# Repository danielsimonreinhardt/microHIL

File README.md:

# microHIL

A small, self-built hardware-in-the-loop box: switchable relays, digital and
analog I/O, two current-monitored 12 V supply outputs and a CAN interface —
all driven from a PC over a single USB cable.

microHIL is built around an **STM32F446RET** (LQFP64) on a custom PCB. It
enumerates as a USB composite device with **two virtual COM ports**: one
carries a plain ASCII command protocol for the I/O, the other exposes CAN1 as
a standard SLCAN adapter. Both can be used at the same time.

> **Status:** working prototype, in active use on the bench. The firmware,
> the command protocol and the Python host library are stable and verified
> against real hardware; the PCB is at revision v0.1 and has a few documented
> quirks that needed rework (see [`docs/hardware-notes.md`](docs/hardware-notes.md)).
> Project documentation under `docs/` is currently in German.

## Features

| Function | Channels | Notes |
|---|---|---|
| Relays | 4 | dry contacts |
| Digital outputs | 8 | `OUT1-8` |
| Digital inputs | 8 | 12 V level, comparator front end with selectable 5 V/12 V threshold |
| Analog inputs | 4 | calibrated, reported in mV (divider for up to ~13 V) |
| Analog outputs | 2 | DAC + buffer, calibrated, ~0…12.2 V |
| Switchable 12 V outputs | 2 | high-side switch with current sense (mA) and firmware current limiting |
| PWM outputs | 4 | 0…1000 ‰, configurable frequency 1 Hz…20 kHz (`PWMFREQ`, shared by all 4 channels, ceiling scope-verified), shares the output stage with `OUT1-4` (interlocked in firmware) |
| CAN | 1 (+1 reserved) | CAN1 as SLCAN USB adapter; CAN2 reserved for remote control |

Analog channels (`AIN1-4`, `AOUT1-2`, `CURR1-2`) are individually two-point
calibrated against reference instruments, so the protocol speaks physical
units (mV / mA) rather than raw ADC counts — see
[`docs/calibration.md`](docs/calibration.md).

The 12 V outputs are protected in firmware: a per-channel limit (`ILIM`,
default 1200 mA) and a combined 1500 mA budget for the shared polyfuse. A
tripped channel latches off until its request is explicitly withdrawn;
`PWR12FLT?` reports the cause.

## Repository layout

```
firmware/microHIL_fw/   STM32CubeMX + CMake project for the STM32F446RET
host/                   Python client library, test GUI, hardware-free checks
hardware/               KiCad 9 schematic, PCB and Gerbers (rev v0.1)
docs/                   Protocol reference, CAN/SLCAN reference, calibration,
                        hardware notes (German)
```

## USB interfaces

microHIL presents two CDC-ACM functions under the same VID:PID `0483:5740`
(ST's factory VCP IDs — no own USB vendor ID). They are told apart by
interface number, which `host/microhil.py` does automatically:

| Interface | Windows | Linux | Content |
|---|---|---|---|
| 0 | `…&MI_00` | `…-if00` | HIL command protocol — [`docs/protocol.md`](docs/protocol.md) |
| 2 | `…&MI_02` | `…-if02` | CAN1 as SLCAN — [`docs/can-usb.md`](docs/can-usb.md) |

Two ports rather than one multiplexed port, because a COM port can only be
opened once on Windows: this way the test GUI and a CAN tool can run
side by side.

## Command protocol

Line-based ASCII, uppercase, `\n`-terminated requests, `\r\n`-terminated
replies — a plain `readline()` is enough. Values are always integers in
mV/mA.

```
*IDN?                 -> microHIL,fw=0.1.0,SN=2065386A5631
RELAY 1 1             -> OK
IN?                   -> 10110001        (IN1 first)
AIN? 2                -> 3300            (mV, calibrated)
PWR12 1 1             -> OK
CURR? 1               -> 536             (mA)
PWM 1 500             -> OK              (‰ duty cycle)
```

Errors are exactly `ERR ARGS`, `ERR RANGE` or `ERR UNKNOWN`. The full
reference, including the range-checking rules and the board serial number in
`*IDN?`, is in [`docs/protocol.md`](docs/protocol.md).

CAN1 speaks the SLCAN/Lawicel dialect (CAN232-compatible), so it works with
`python-can` (`interface="slcan"`) and, on Linux, as a regular SocketCAN
interface via `slcand`. Two extensions beyond CAN232: `B<bit/s>` for exact
non-standard bitrates and `Y` for a loopback self-test without a bus. See
[`docs/can-usb.md`](docs/can-usb.md).

## Getting started (host)

```bash
pip install -r host/requirements.txt
```

```python
from host.microhil import MicroHIL

with MicroHIL() as hil:          # finds the right COM port by itself
    print(hil.idn())
    hil.set_relay(1, True)
    print(hil.get_ain_mv(2), "mV")
    hil.set_pwr12(1, True)
    print(hil.get_curr_ma(1), "mA")
```

A PySide6 test GUI that exercises every function manually, with a CAN trace
tab, comes with it:

```bash
python host/gui.py
```

Two checks in `host/tests/` run without any hardware attached — they verify
the CAN bit timing against the bxCAN register limits and the SLCAN wire
format in both directions against the real `python-can` driver:

```bash
python host/tests/check_bit_timing.py
python host/tests/check_slcan_wire.py
```

## Building the firmware

Needs the `arm-none-eabi` GCC toolchain, CMake ≥ 3.22 and Ninja. The project
was generated with STM32CubeMX and is set up for the STM32Cube extension for
VS Code, but builds fine from the command line:

```bash
cd firmware/microHIL_fw
cmake --preset Debug
cmake --build --preset Debug
```

Flashing is over SWD with an ST-Link V2, e.g.:

```bash
STM32_Programmer_CLI -c port=SWD -w build/Debug/microHIL_fw.elf -rst
```

With GCC 10.3.1 (the version bundled with STM32CubeIDE 1.10.1, confirmed
working end-to-end 2026-09-09), the linker fails on all three `.ld` files
with `non constant or forward reference address expression for section
.ARM.extab` — the `(READONLY)` section attribute on `.ARM.extab`/`.ARM`/
`.preinit_array`/`.init_array`/`.fini_array` needs GCC 11+ (each occurrence
says so in its own comment). Remove `(READONLY)` from those five section
headers in `STM32F446xx_FLASH.ld` (used by the CMake build) and, for
STM32CubeIDE's own Eclipse build, `STM32F446RETX_FLASH.ld`/`_RAM.ld` too, if
building with GCC 10. A GCC 11+ toolchain doesn't need this.

If you regenerate from `microHIL_fw.ioc`, note that the CAN bit timing is
computed at runtime in `Core/Src/slcan.c` (deliberately not stored in CubeMX)
and that the CDC composite build needs ST's `CompositeBuilder`, which CubeMX
does not emit for the F4 series — it is vendored in
`Middlewares/ST/STM32_USB_Device_Library/Class/CompositeBuilder/`.

## Hardware

- MCU: STM32F446RET, LQFP64, 8 MHz crystal, HSE/PLL clock tree
- Debug: SWD (ST-Link V2)
- CAN1: PB8/PB9, transceiver and 120 Ω termination populated
- CAN2: PB5/PB6, not in service yet (see Roadmap)
- KiCad sources, PCB and Gerbers for rev v0.1 are in [`hardware/`](hardware/)

Board revision v0.1 has known issues that required rework — most notably VBUS
routed straight onto the supply rail, and missing pulldowns on the digital
input comparator stages. All of them are documented, with measurements and
the fixes applied, in [`docs/hardware-notes.md`](docs/hardware-notes.md).
Read that file before building a board from these files.

## Roadmap

- **CAN2 as a remote-control interface.** Drive microHIL from a supervising
  ECU or test bench with the same functions as the USB command protocol.
  Frame layout, addressing and bitrate are still to be defined; the bxCAN
  filter bank split needed for CAN2 to receive at all is already in place
  (`SlaveStartFilterBank = 14` in `Core/Src/can_if.c`).
- **CAN1 against a second real bus node**, plus a scope measurement of the
  actual bit rate.

## License

MIT — see [LICENSE](LICENSE).

Vendored third-party code keeps its own license: the STM32 HAL drivers, CMSIS
and the ST USB device library under `firmware/microHIL_fw/Drivers/` and
`firmware/microHIL_fw/Middlewares/` are © STMicroelectronics / Arm and
licensed under their respective terms (see the `LICENSE.txt` files in those
directories).

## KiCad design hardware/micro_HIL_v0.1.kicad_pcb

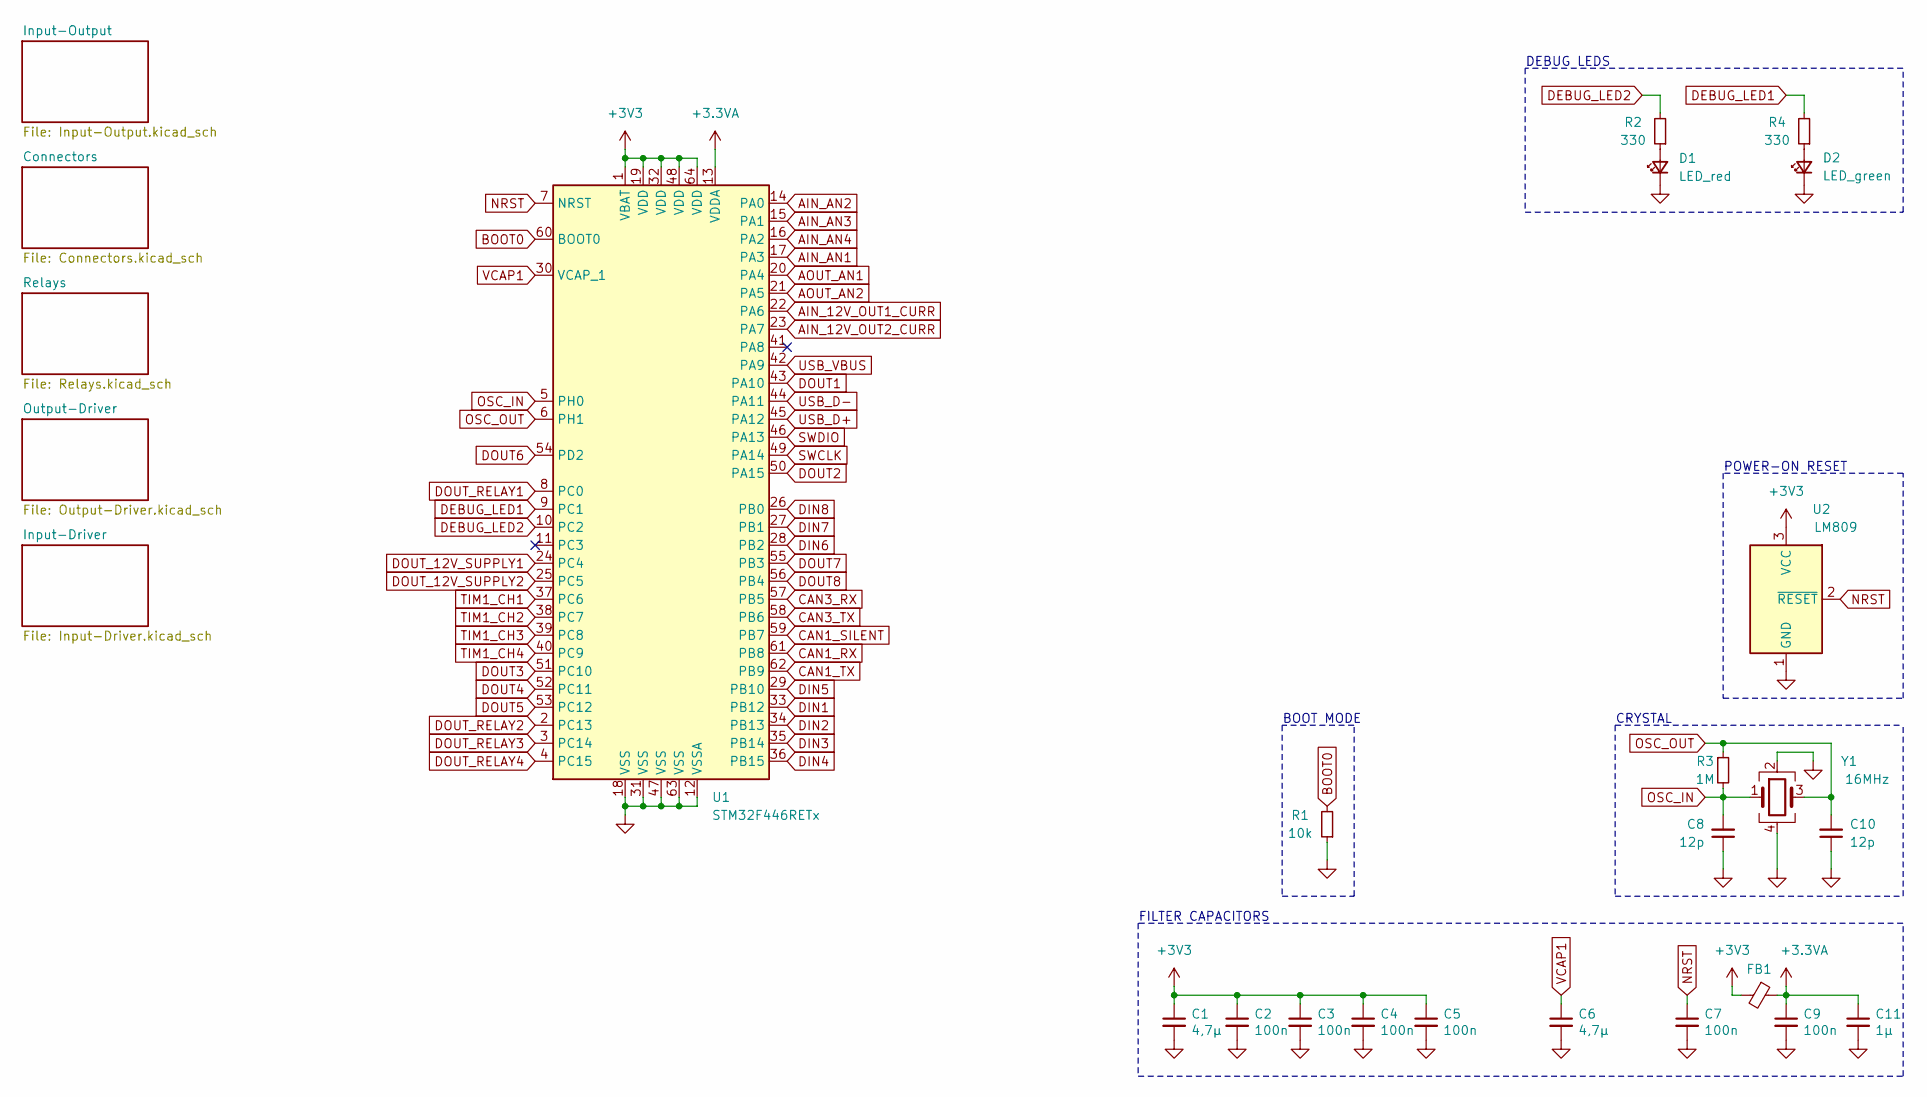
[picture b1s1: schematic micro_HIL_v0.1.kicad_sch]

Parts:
C1, C6: 4,7µ; C_0805_2012Metric
C2, C3, C4, C5, C7, C9: 100n; C_0603_1608Metric
C8, C10: 12p; C_0603_1608Metric
C11: 1µ; C_0603_1608Metric
D1: LED_red; LED_0805_2012Metric
D2: LED_green; LED_0805_2012Metric
FB1: Ferrite_Bead_Small; L_0805_2012Metric
R1: 10k; R_0603_1608Metric
R2, R4: 330; R_0603_1608Metric
R3: 1M; R_0603_1608Metric
U1: STM32F446RETx; LQFP-64_10x10mm_P0.5mm
U2: LM809; SOT-23
Y1: 16MHz; Crystal_SMD_3225-4Pin_3.2x2.5mm

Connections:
+3.3VA: C9.1, C11.1, FB1.1, U1.13 (VDDA)
+3V3: C1.1, C2.1, C3.1, C4.1, C5.1, FB1.2, U1.1 (VBAT), U1.19 (VDD), U1.32 (VDD), U1.48 (VDD), U1.64 (VDD), U2.3 (VCC); also elsewhere on the board
AIN_12V_OUT1_CURR: U1.22 (PA6); also elsewhere on the board
AIN_12V_OUT2_CURR: U1.23 (PA7); also elsewhere on the board
AIN_AN1: U1.17 (PA3); also elsewhere on the board
AIN_AN2: U1.14 (PA0); also elsewhere on the board
AIN_AN3: U1.15 (PA1); also elsewhere on the board
AIN_AN4: U1.16 (PA2); also elsewhere on the board
AOUT_AN1: U1.20 (PA4); also elsewhere on the board
AOUT_AN2: U1.21 (PA5); also elsewhere on the board
BOOT0: R1.2, U1.60 (BOOT0)
CAN1_RX: U1.61 (PB8); also elsewhere on the board
CAN1_SILENT: U1.59 (PB7); also elsewhere on the board
CAN1_TX: U1.62 (PB9); also elsewhere on the board
CAN3_RX: U1.57 (PB5); also elsewhere on the board
CAN3_TX: U1.58 (PB6); also elsewhere on the board
DEBUG_LED1: R4.2, U1.9 (PC1)
DEBUG_LED2: R2.2, U1.10 (PC2)
DIN1: U1.33 (PB12); also elsewhere on the board
DIN2: U1.34 (PB13); also elsewhere on the board
DIN3: U1.35 (PB14); also elsewhere on the board
DIN4: U1.36 (PB15); also elsewhere on the board
DIN5: U1.29 (PB10); also elsewhere on the board
DIN6: U1.28 (PB2); also elsewhere on the board
DIN7: U1.27 (PB1); also elsewhere on the board
DIN8: U1.26 (PB0); also elsewhere on the board
DOUT1: U1.43 (PA10); also elsewhere on the board
DOUT2: U1.50 (PA15); also elsewhere on the board
DOUT3: U1.51 (PC10); also elsewhere on the board
DOUT4: U1.52 (PC11); also elsewhere on the board
DOUT5: U1.53 (PC12); also elsewhere on the board
DOUT6: U1.54 (PD2); also elsewhere on the board
DOUT7: U1.55 (PB3); also elsewhere on the board
DOUT8: U1.56 (PB4); also elsewhere on the board
DOUT_12V_SUPPLY1: U1.24 (PC4); also elsewhere on the board
DOUT_12V_SUPPLY2: U1.25 (PC5); also elsewhere on the board
DOUT_RELAY1: U1.8 (PC0); also elsewhere on the board
DOUT_RELAY2: U1.2 (PC13); also elsewhere on the board
DOUT_RELAY3: U1.3 (PC14); also elsewhere on the board
DOUT_RELAY4: U1.4 (PC15); also elsewhere on the board
GND: C1.2, C2.2, C3.2, C4.2, C5.2, C6.2, C7.2, C8.1, C9.2, C10.1, C11.2, D1.1 (K), D2.1 (K), R1.1, U1.12 (VSSA), U1.18 (VSS), U1.31 (VSS), U1.47 (VSS), U1.63 (VSS), U2.1 (GND), Y1.2, Y1.4; also elsewhere on the board
NRST: C7.1, U1.7 (NRST), U2.2 (~RESET); also elsewhere on the board
unnamed: D1.2 (A), R2.1
unnamed: D2.2 (A), R4.1
OSC_IN: C8.2, R3.2, U1.5 (PH0), Y1.1
OSC_OUT: C10.2, R3.1, U1.6 (PH1), Y1.3
SWCLK: U1.49 (PA14); also elsewhere on the board
SWDIO: U1.46 (PA13); also elsewhere on the board
TIM1_CH1: U1.37 (PC6); also elsewhere on the board
TIM1_CH2: U1.38 (PC7); also elsewhere on the board
TIM1_CH3: U1.39 (PC8); also elsewhere on the board
TIM1_CH4: U1.40 (PC9); also elsewhere on the board
USB_D+: U1.45 (PA12); also elsewhere on the board
USB_D-: U1.44 (PA11); also elsewhere on the board
USB_VBUS: U1.42 (PA9); also elsewhere on the board
VCAP1: C6.1, U1.30 (VCAP_1)

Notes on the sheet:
POWER-ON RESET
BOOT MODE
DEBUG LEDS
FILTER CAPACITORS
CRYSTAL

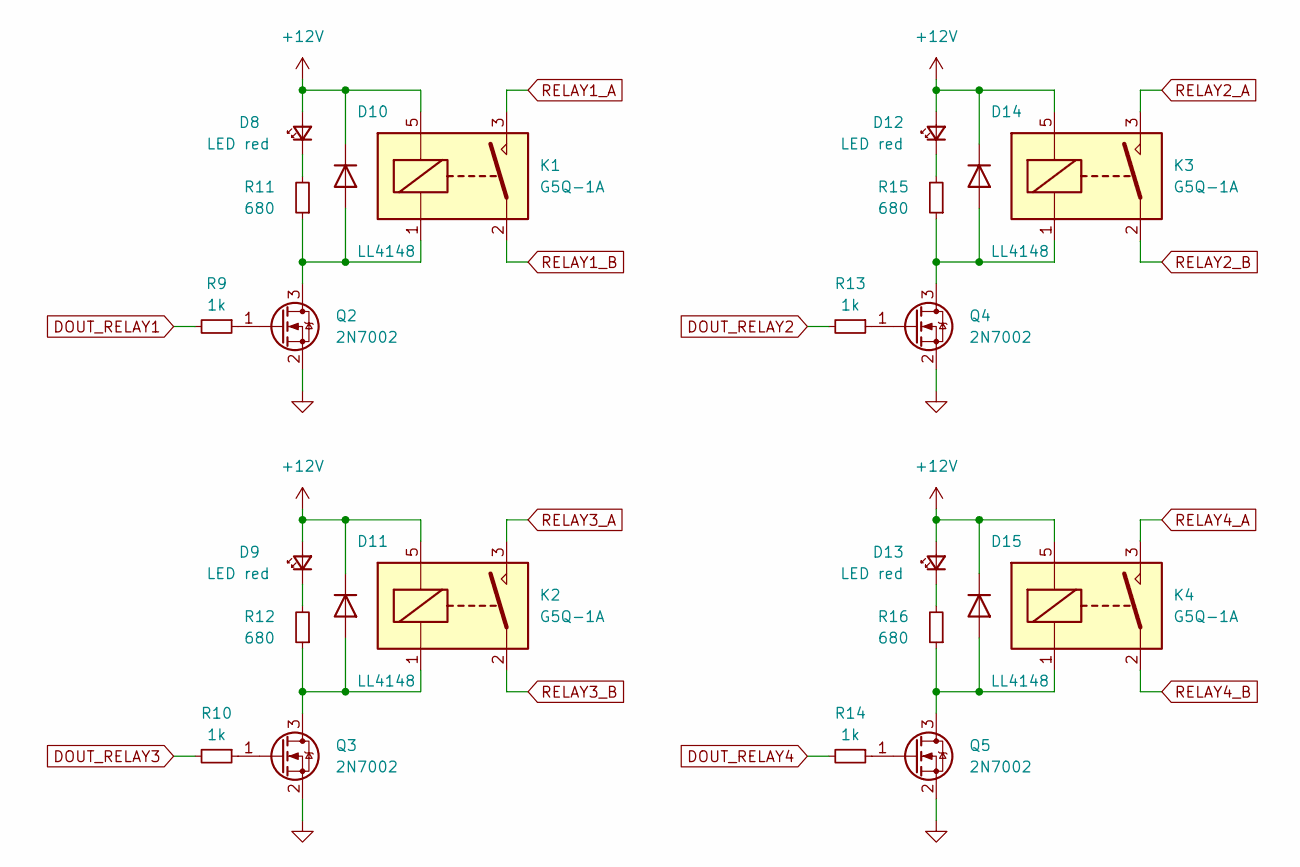
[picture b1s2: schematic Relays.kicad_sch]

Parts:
D8, D9, D12, D13: LED red; LED_D5.0mm
D10, D11, D14, D15: LL4148; D_MiniMELF
K1, K2, K3, K4: G5Q-1A; Relay_SPST_Omron-G5Q-1A
Q2, Q3, Q4, Q5: 2N7002; SOT-23
R9, R10, R13, R14: 1k; R_0603_1608Metric
R11, R12, R15, R16: 680; R_0603_1608Metric

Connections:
+12V: D8.2 (A), D9.2 (A), D10.1 (K), D11.1 (K), D12.2 (A), D13.2 (A), D14.1 (K), D15.1 (K), K1.5, K2.5, K3.5, K4.5; also elsewhere on the board
DOUT_RELAY1: R9.2; also elsewhere on the board
DOUT_RELAY2: R13.2; also elsewhere on the board
DOUT_RELAY3: R10.2; also elsewhere on the board
DOUT_RELAY4: R14.2; also elsewhere on the board
GND: Q2.2 (S), Q3.2 (S), Q4.2 (S), Q5.2 (S); also elsewhere on the board
unnamed: D8.1 (K), R11.2
unnamed: D9.1 (K), R12.2
unnamed: D10.2 (A), K1.1, Q2.3 (D), R11.1
unnamed: D11.2 (A), K2.1, Q3.3 (D), R12.1
unnamed: D12.1 (K), R15.2
unnamed: D13.1 (K), R16.2
unnamed: D14.2 (A), K3.1, Q4.3 (D), R15.1
unnamed: D15.2 (A), K4.1, Q5.3 (D), R16.1
unnamed: Q2.1 (G), R9.1
unnamed: Q3.1 (G), R10.1
unnamed: Q4.1 (G), R13.1
unnamed: Q5.1 (G), R14.1
RELAY1_A: K1.3; also elsewhere on the board
RELAY1_B: K1.2; also elsewhere on the board
RELAY2_A: K3.3; also elsewhere on the board
RELAY2_B: K3.2; also elsewhere on the board
RELAY3_A: K2.3; also elsewhere on the board
RELAY3_B: K2.2; also elsewhere on the board
RELAY4_A: K4.3; also elsewhere on the board
RELAY4_B: K4.2; also elsewhere on the board

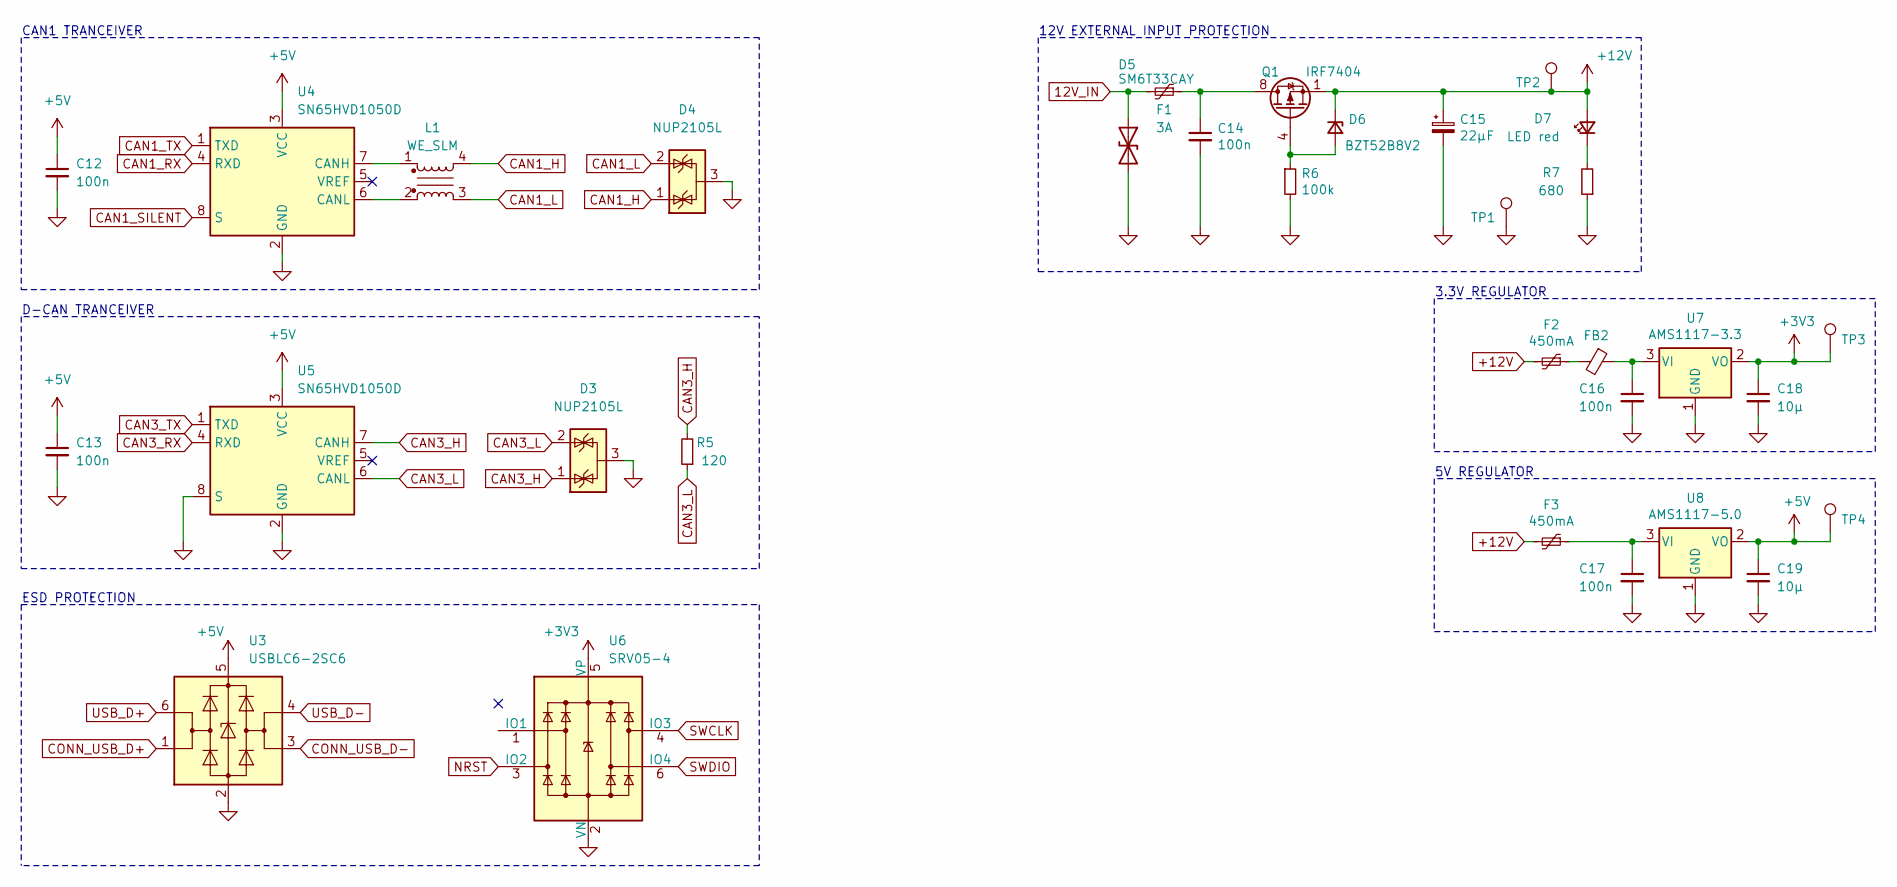
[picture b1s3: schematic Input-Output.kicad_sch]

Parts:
C12, C13, C14, C16, C17: 100n; C_0603_1608Metric
C15: 22µF; CP_Elec_6.3x5.9
C18, C19: 10µ; C_0805_2012Metric
D3, D4: NUP2105L; SOT-23
D5: SM6T33CAY; D_SMB_Handsoldering
D6: BZT52B8V2; D_SOD-123
D7: LED red; LED_D5.0mm
F1: 3A; Fuse_1812_4532Metric
F2, F3: 450mA; Fuse_1210_3225Metric
FB2: Ferrite_Bead_Small; L_0805_2012Metric
L1: WE_SLM; L_CommonMode_Wuerth_WE-SLM
Q1: IRF7404; SOIC-8_3.9x4.9mm_P1.27mm
R5: 120; R_0603_1608Metric
R6: 100k; R_0603_1608Metric
R7: 680; R_0603_1608Metric
TP1: TestPoint; Pin_D1.1mm_L8.5mm_W2.5mm_FlatFork
TP2, TP3, TP4: TestPoint; TestPoint_Pad_D1.0mm
U3: USBLC6-2SC6; SOT-23-6
U4, U5: SN65HVD1050D; SOIC-8_3.9x4.9mm_P1.27mm
U6: SRV05-4; SOT-23-6
U7: AMS1117-3.3; SOT-223-3_TabPin2
U8: AMS1117-5.0; SOT-223-3_TabPin2

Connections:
12V_IN: D5.1 (A1), F1.2; also elsewhere on the board
+3V3: C18.1, TP3.1, U6.5 (VP), U7.2 (VO); also elsewhere on the board
+5V: C12.1, C13.1, C19.1, TP4.1, U3.5 (VBUS), U4.3 (VCC), U5.3 (VCC), U8.2 (VO); also elsewhere on the board
+12V: C15.1, D6.1 (K), D7.2 (A), F2.2, F3.2, Q1.1 (S), Q1.2 (S), Q1.3 (S), TP2.1; also elsewhere on the board
CAN1_H: D4.1 (K), L1.4; also elsewhere on the board
CAN1_L: D4.2 (K), L1.3; also elsewhere on the board
CAN1_RX: U4.4 (RXD); also elsewhere on the board
CAN1_SILENT: U4.8 (S); also elsewhere on the board
CAN1_TX: U4.1 (TXD); also elsewhere on the board
CAN3_H: D3.1 (K), R5.2, U5.7 (CANH); also elsewhere on the board
CAN3_L: D3.2 (K), R5.1, U5.6 (CANL); also elsewhere on the board
CAN3_RX: U5.4 (RXD); also elsewhere on the board
CAN3_TX: U5.1 (TXD); also elsewhere on the board
CONN_USB_D+: U3.1 (I/O1); also elsewhere on the board
CONN_USB_D-: U3.3 (I/O2); also elsewhere on the board
GND: C12.2, C13.2, C14.2, C15.2, C16.2, C17.2, C18.2, C19.2, D3.3 (A), D4.3 (A), D5.2 (A2), R6.2, R7.1, TP1.1, U3.2 (GND), U4.2 (GND), U5.2 (GND), U5.8 (S), U6.2 (VN), U7.1 (GND), U8.1 (GND); also elsewhere on the board
NRST: U6.3 (IO2); also elsewhere on the board
unnamed: C14.1, F1.1, Q1.5 (D), Q1.6 (D), Q1.7 (D), Q1.8 (D)
unnamed: C16.1, FB2.1, U7.3 (VI)
unnamed: C17.1, F3.1, U8.3 (VI)
unnamed: D6.2 (A), Q1.4 (G), R6.1
unnamed: D7.1 (K), R7.2
unnamed: F2.1, FB2.2
unnamed: L1.1, U4.7 (CANH)
unnamed: L1.2, U4.6 (CANL)
SWCLK: U6.4 (IO3); also elsewhere on the board
SWDIO: U6.6 (IO4); also elsewhere on the board
USB_D+: U3.6 (I/O1); also elsewhere on the board
USB_D-: U3.4 (I/O2); also elsewhere on the board

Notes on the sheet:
12V EXTERNAL INPUT PROTECTION
5V REGULATOR
3.3V REGULATOR
D-CAN TRANCEIVER
CAN1 TRANCEIVER
ESD PROTECTION

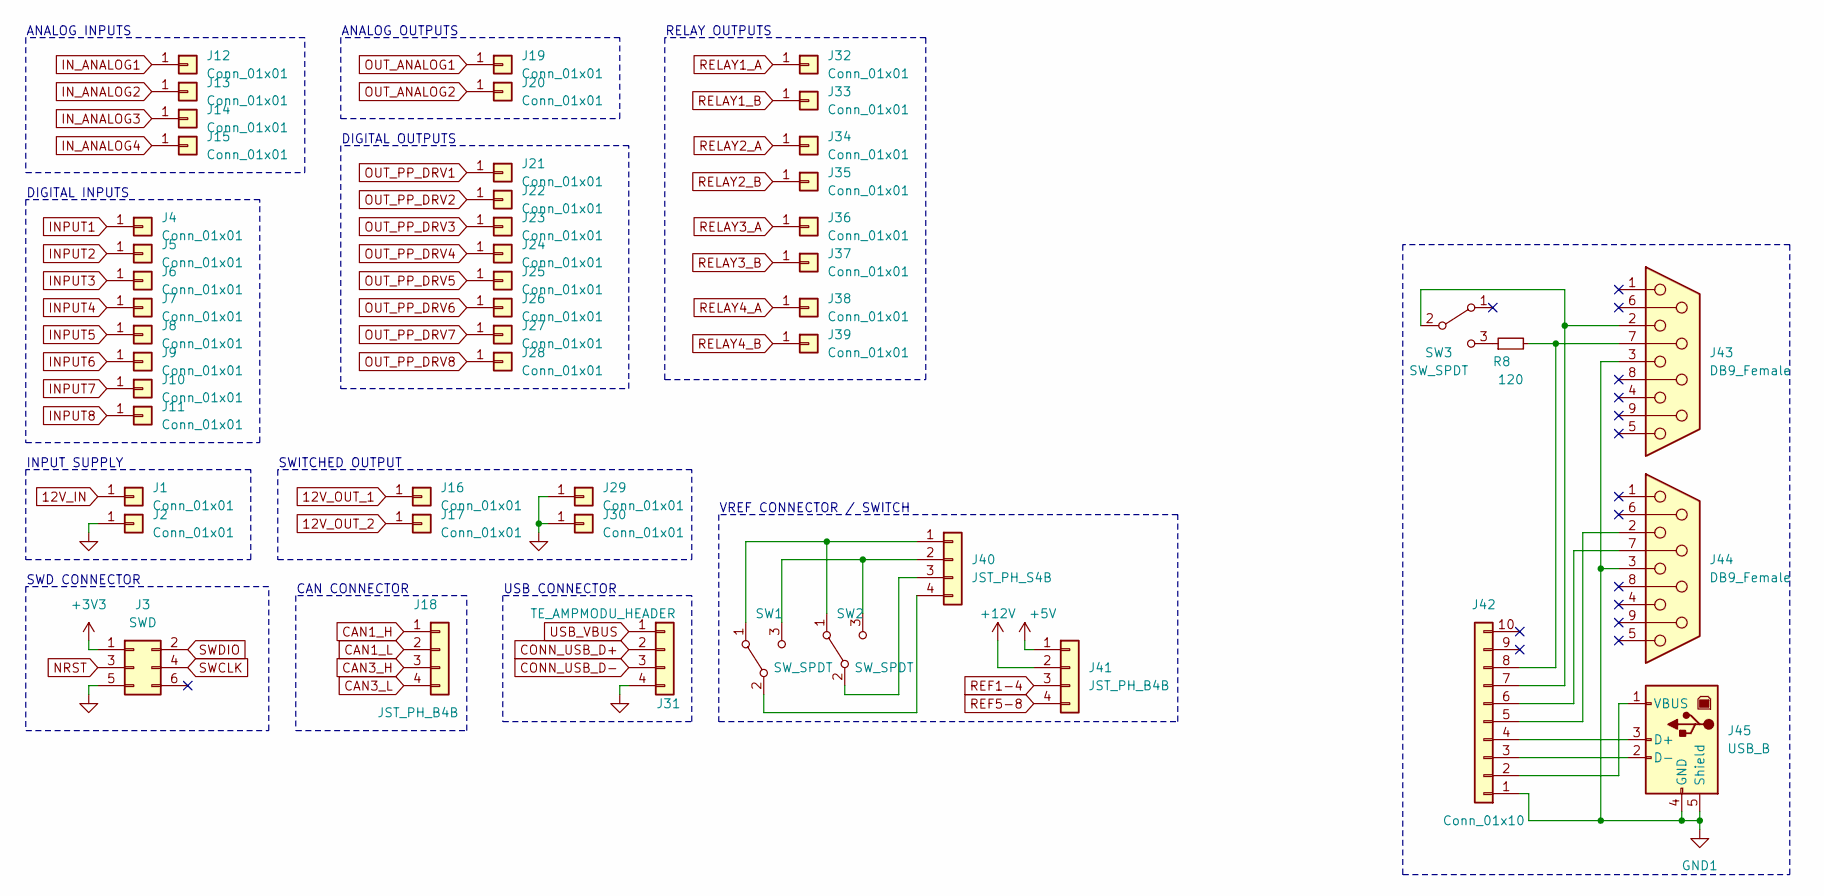
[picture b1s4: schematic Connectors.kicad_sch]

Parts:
J1, J2, J4, J5, J6, J7, J8, J9, J10, J11, J12, J13, J14, J15, J16, J17, J19, J20, J21, J22, J23, J24, J25, J26, J27, J28, J29, J30, J32, J33, J34, J35, J36, J37, J38, J39: Conn_01x01; Hirschmann_SEP_2630_S1,9
J3: SWD; IDC-Header_2x03_P2.54mm_Vertical
J18, J41: JST_PH_B4B; JST_PH_B4B-PH-K_1x04_P2.00mm_Vertical
J31: TE_AMPMODU_HEADER; PinHeader_1x04_P2.54mm_Vertical
J40: JST_PH_S4B; JST_PH_S4B-PH-K_1x04_P2.00mm_Horizontal
J42: Conn_01x10; TE_3-1445056-0
J43, J44: DB9_Female; DSUB-9_Female_Vertical_P2.77x2.84mm_MountingHoles
J45: USB_B; USB_B_TE_5787834_Vertical
R8: 120; R_0603_1608Metric
SW1, SW2, SW3: SW_SPDT; TerminalBlock_bornier-3_P5.08mm

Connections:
12V_IN: J1.1; also elsewhere on the board
12V_OUT_1: J16.1; also elsewhere on the board
12V_OUT_2: J17.1; also elsewhere on the board
+3V3: J3.1; also elsewhere on the board
+5V: J41.1; also elsewhere on the board
+12V: J41.2; also elsewhere on the board
CAN1_H: J18.1; also elsewhere on the board
CAN1_L: J18.2; also elsewhere on the board
CAN3_H: J18.3; also elsewhere on the board
CAN3_L: J18.4; also elsewhere on the board
CONN_USB_D+: J31.2; also elsewhere on the board
CONN_USB_D-: J31.3; also elsewhere on the board
GND: J2.1, J3.5, J29.1, J30.1, J31.4; also elsewhere on the board
GND1: J42.1, J43.3, J44.3, J45.4 (GND), J45.5 (Shield)
INPUT1: J4.1; also elsewhere on the board
INPUT2: J5.1; also elsewhere on the board
INPUT3: J6.1; also elsewhere on the board
INPUT4: J7.1; also elsewhere on the board
INPUT5: J8.1; also elsewhere on the board
INPUT6: J9.1; also elsewhere on the board
INPUT7: J10.1; also elsewhere on the board
INPUT8: J11.1; also elsewhere on the board
IN_ANALOG1: J12.1; also elsewhere on the board
IN_ANALOG2: J13.1; also elsewhere on the board
IN_ANALOG3: J14.1; also elsewhere on the board
IN_ANALOG4: J15.1; also elsewhere on the board
NRST: J3.3; also elsewhere on the board
unnamed: J40.1, SW1.1 (A), SW2.1 (A)
unnamed: J40.2, SW1.3 (C), SW2.3 (C)
unnamed: J40.3, SW2.2 (B)
unnamed: J40.4, SW1.2 (B)
unnamed: J42.2, J45.1 (VBUS)
unnamed: J42.3, J45.2 (D-)
unnamed: J42.4, J45.3 (D+)
unnamed: J42.5, J44.2
unnamed: J42.6, J44.7
unnamed: J42.7, J43.2, SW3.2 (B)
unnamed: J42.8, J43.7, R8.2
unnamed: R8.1, SW3.3 (C)
OUT_ANALOG1: J19.1; also elsewhere on the board
OUT_ANALOG2: J20.1; also elsewhere on the board
OUT_PP_DRV1: J21.1; also elsewhere on the board
OUT_PP_DRV2: J22.1; also elsewhere on the board
OUT_PP_DRV3: J23.1; also elsewhere on the board
OUT_PP_DRV4: J24.1; also elsewhere on the board
OUT_PP_DRV5: J25.1; also elsewhere on the board
OUT_PP_DRV6: J26.1; also elsewhere on the board
OUT_PP_DRV7: J27.1; also elsewhere on the board
OUT_PP_DRV8: J28.1; also elsewhere on the board
REF1-4: J41.3; also elsewhere on the board
REF5-8: J41.4; also elsewhere on the board
RELAY1_A: J32.1; also elsewhere on the board
RELAY1_B: J33.1; also elsewhere on the board
RELAY2_A: J34.1; also elsewhere on the board
RELAY2_B: J35.1; also elsewhere on the board
RELAY3_A: J36.1; also elsewhere on the board
RELAY3_B: J37.1; also elsewhere on the board
RELAY4_A: J38.1; also elsewhere on the board
RELAY4_B: J39.1; also elsewhere on the board
SWCLK: J3.4; also elsewhere on the board
SWDIO: J3.2; also elsewhere on the board
USB_VBUS: J31.1; also elsewhere on the board

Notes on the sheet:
ANALOG OUTPUTS
RELAY OUTPUTS
SWD CONNECTOR
DIGITAL INPUTS
USB CONNECTOR
ANALOG INPUTS
SWITCHED OUTPUT
CAN CONNECTOR
VREF CONNECTOR / SWITCH
DIGITAL OUTPUTS
INPUT SUPPLY

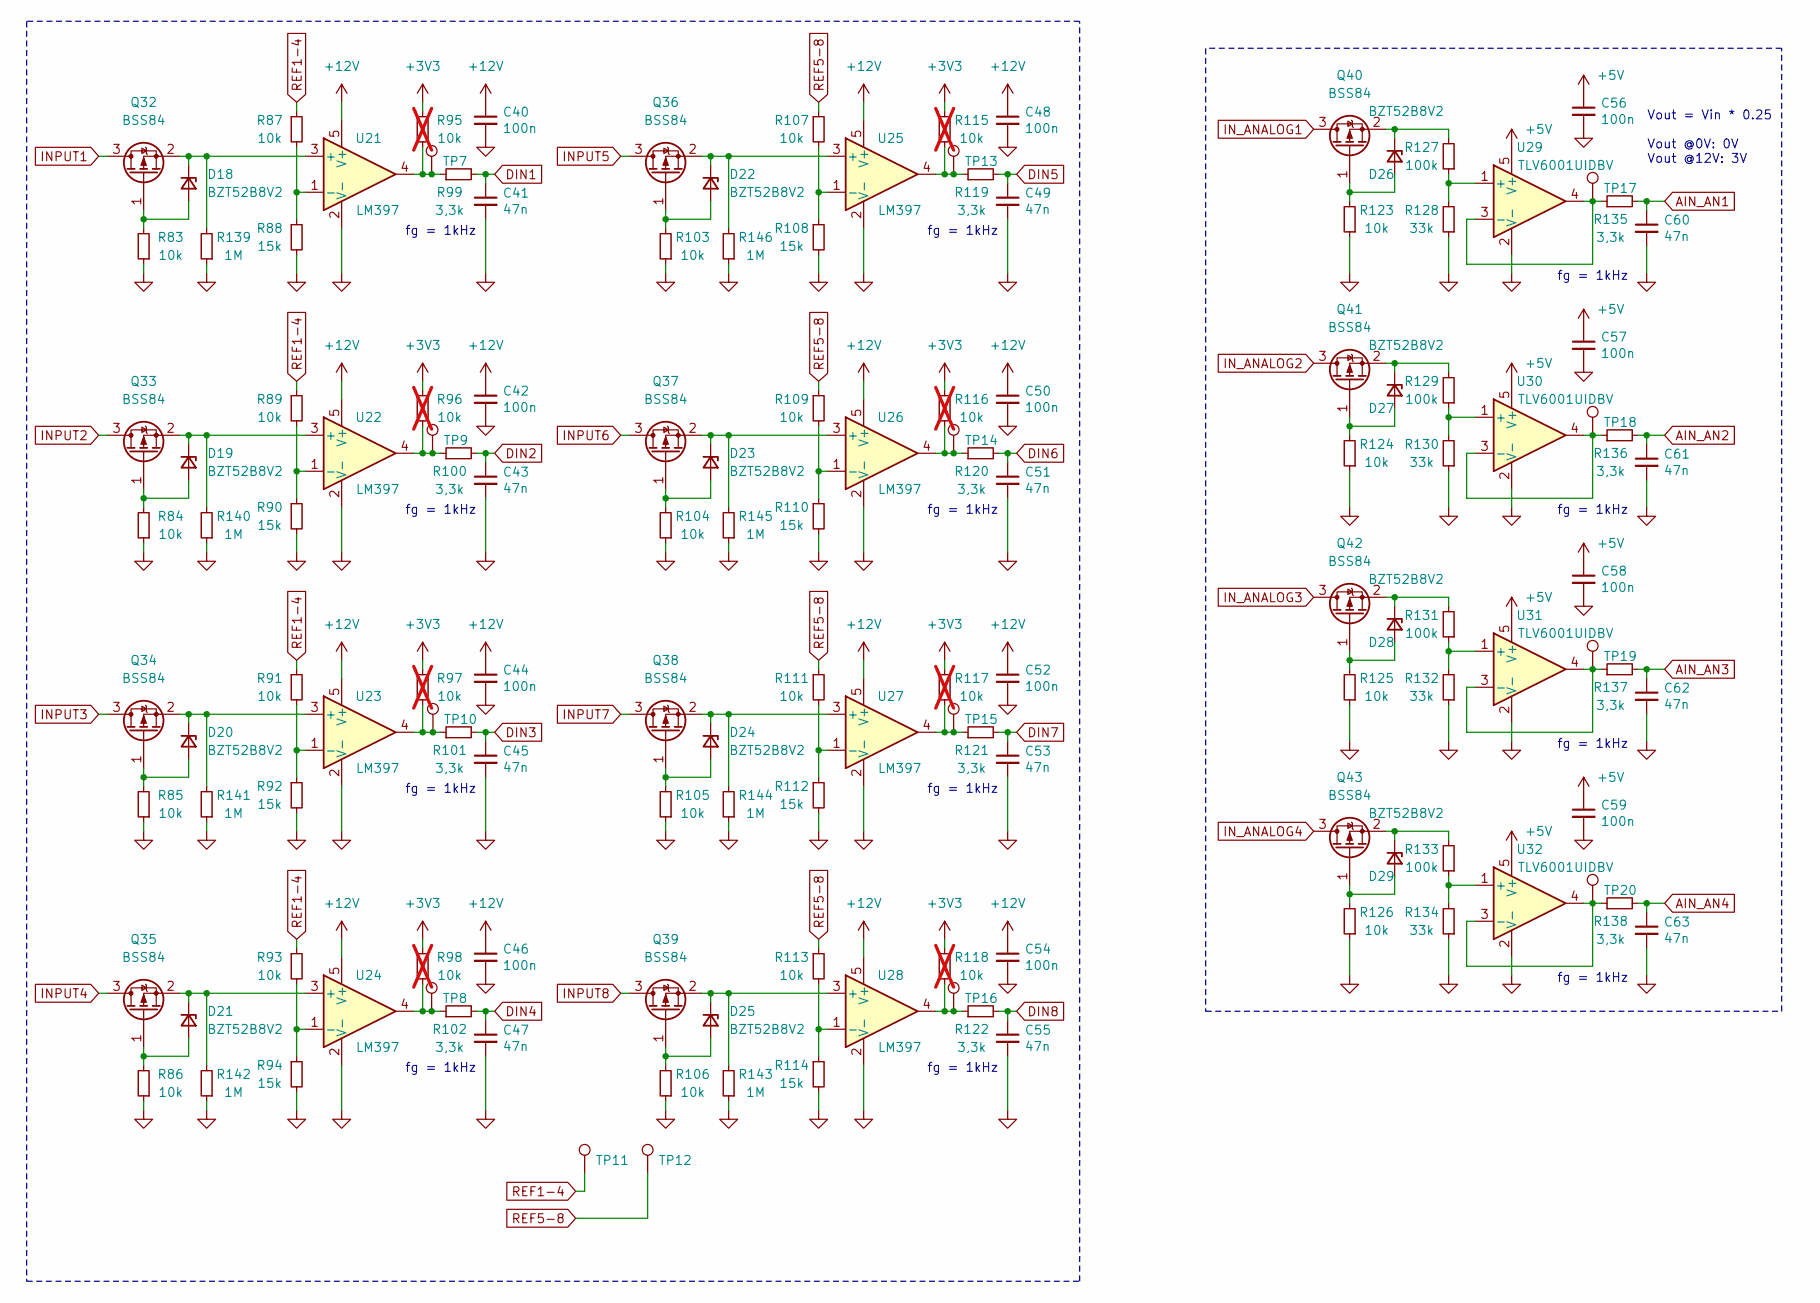
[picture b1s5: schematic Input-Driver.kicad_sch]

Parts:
C40, C42, C44, C46, C48, C50, C52, C54, C56, C57, C58, C59: 100n; C_0603_1608Metric
C41, C43, C45, C47, C49, C51, C53, C55, C60, C61, C62, C63: 47n; C_0603_1608Metric
D18, D19, D20, D21, D22, D23, D24, D25, D26, D27, D28, D29: BZT52B8V2; D_SOD-123
Q32, Q33, Q34, Q35, Q36, Q37, Q38, Q39, Q40, Q41, Q42, Q43: BSS84; SOT-23
R83, R84, R85, R86, R87, R89, R91, R93, R103, R104, R105, R106, R107, R109, R111, R113, R123, R124, R125, R126: 10k; R_0603_1608Metric
R88, R90, R92, R94, R108, R110, R112, R114: 15k; R_0603_1608Metric
R95, R96, R97, R98, R115, R116, R117, R118: 10k; R_0603_1608Metric; not fitted
R99, R100, R101, R102, R119, R120, R121, R122, R135, R136, R137, R138: 3,3k; R_0603_1608Metric
R127, R129, R131, R133: 100k; R_0603_1608Metric
R128, R130, R132, R134: 33k; R_0603_1608Metric
R139, R140, R141, R142, R143, R144, R145, R146: 1M; R_0603_1608Metric
TP7, TP8, TP9, TP10, TP11, TP12, TP13, TP14, TP15, TP16, TP17, TP18, TP19, TP20: TestPoint; TestPoint_Pad_D1.0mm
U21, U22, U23, U24, U25, U26, U27, U28: LM397; SOT-23-5
U29, U30, U31, U32: TLV6001UIDBV; SOT-23-5

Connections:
+3V3: R95.2, R96.2, R97.2, R98.2, R115.2, R116.2, R117.2, R118.2; also elsewhere on the board
+5V: C56.1, C57.1, C58.1, C59.1, U29.5 (V+), U30.5 (V+), U31.5 (V+), U32.5 (V+); also elsewhere on the board
+12V: C40.1, C42.1, C44.1, C46.1, C48.1, C50.1, C52.1, C54.1, U21.5 (V+), U22.5 (V+), U23.5 (V+), U24.5 (V+), U25.5 (V+), U26.5 (V+), U27.5 (V+), U28.5 (V+); also elsewhere on the board
AIN_AN1: C60.1, R135.2; also elsewhere on the board
AIN_AN2: C61.1, R136.2; also elsewhere on the board
AIN_AN3: C62.1, R137.2; also elsewhere on the board
AIN_AN4: C63.1, R138.2; also elsewhere on the board
DIN1: C41.1, R99.2; also elsewhere on the board
DIN2: C43.1, R100.2; also elsewhere on the board
DIN3: C45.1, R101.2; also elsewhere on the board
DIN4: C47.1, R102.2; also elsewhere on the board
DIN5: C49.1, R119.2; also elsewhere on the board
DIN6: C51.1, R120.2; also elsewhere on the board
DIN7: C53.1, R121.2; also elsewhere on the board
DIN8: C55.1, R122.2; also elsewhere on the board
GND: C40.2, C41.2, C42.2, C43.2, C44.2, C45.2, C46.2, C47.2, C48.2, C49.2, C50.2, C51.2, C52.2, C53.2, C54.2, C55.2, C56.2, C57.2, C58.2, C59.2, C60.2, C61.2, C62.2, C63.2, R83.1, R84.1, R85.1, R86.1, R88.2, R90.2, R92.2, R94.2, R103.1, R104.1, R105.1, R106.1, R108.2, R110.2, R112.2, R114.2, R123.1, R124.1, R125.1, R126.1, R128.1, R130.1, R132.1, R134.1, R139.1, R140.1, R141.1, R142.1, R143.1, R144.1, R145.1, R146.1, U21.2 (V-), U22.2 (V-), U23.2 (V-), U24.2 (V-), U25.2 (V-), U26.2 (V-), U27.2 (V-), U28.2 (V-), U29.2 (V-), U30.2 (V-), U31.2 (V-), U32.2 (V-); also elsewhere on the board
INPUT1: Q32.3 (D); also elsewhere on the board
INPUT2: Q33.3 (D); also elsewhere on the board
INPUT3: Q34.3 (D); also elsewhere on the board
INPUT4: Q35.3 (D); also elsewhere on the board
INPUT5: Q36.3 (D); also elsewhere on the board
INPUT6: Q37.3 (D); also elsewhere on the board
INPUT7: Q38.3 (D); also elsewhere on the board
INPUT8: Q39.3 (D); also elsewhere on the board
IN_ANALOG1: Q40.3 (D); also elsewhere on the board
IN_ANALOG2: Q41.3 (D); also elsewhere on the board
IN_ANALOG3: Q42.3 (D); also elsewhere on the board
IN_ANALOG4: Q43.3 (D); also elsewhere on the board
unnamed: D18.1 (K), Q32.2 (S), R139.2, U21.3 (+)
unnamed: D18.2 (A), Q32.1 (G), R83.2
unnamed: D19.1 (K), Q33.2 (S), R140.2, U22.3 (+)
unnamed: D19.2 (A), Q33.1 (G), R84.2
unnamed: D20.1 (K), Q34.2 (S), R141.2, U23.3 (+)
unnamed: D20.2 (A), Q34.1 (G), R85.2
unnamed: D21.1 (K), Q35.2 (S), R142.2, U24.3 (+)
unnamed: D21.2 (A), Q35.1 (G), R86.2
unnamed: D22.1 (K), Q36.2 (S), R146.2, U25.3 (+)
unnamed: D22.2 (A), Q36.1 (G), R103.2
unnamed: D23.1 (K), Q37.2 (S), R145.2, U26.3 (+)
unnamed: D23.2 (A), Q37.1 (G), R104.2
unnamed: D24.1 (K), Q38.2 (S), R144.2, U27.3 (+)
unnamed: D24.2 (A), Q38.1 (G), R105.2
unnamed: D25.1 (K), Q39.2 (S), R143.2, U28.3 (+)
unnamed: D25.2 (A), Q39.1 (G), R106.2
unnamed: D26.1 (K), Q40.2 (S), R127.2
unnamed: D26.2 (A), Q40.1 (G), R123.2
unnamed: D27.1 (K), Q41.2 (S), R129.2
unnamed: D27.2 (A), Q41.1 (G), R124.2
unnamed: D28.1 (K), Q42.2 (S), R131.2
unnamed: D28.2 (A), Q42.1 (G), R125.2
unnamed: D29.1 (K), Q43.2 (S), R133.2
unnamed: D29.2 (A), Q43.1 (G), R126.2
unnamed: R87.2, R88.1, U21.1 (-)
unnamed: R89.2, R90.1, U22.1 (-)
unnamed: R91.2, R92.1, U23.1 (-)
unnamed: R93.2, R94.1, U24.1 (-)
unnamed: R95.1, R99.1, TP7.1, U21.4
unnamed: R96.1, R100.1, TP9.1, U22.4
unnamed: R97.1, R101.1, TP10.1, U23.4
unnamed: R98.1, R102.1, TP8.1, U24.4
unnamed: R107.2, R108.1, U25.1 (-)
unnamed: R109.2, R110.1, U26.1 (-)
unnamed: R111.2, R112.1, U27.1 (-)
unnamed: R113.2, R114.1, U28.1 (-)
unnamed: R115.1, R119.1, TP13.1, U25.4
unnamed: R116.1, R120.1, TP14.1, U26.4
unnamed: R117.1, R121.1, TP15.1, U27.4
unnamed: R118.1, R122.1, TP16.1, U28.4
unnamed: R127.1, R128.2, U29.1 (+)
unnamed: R129.1, R130.2, U30.1 (+)
unnamed: R131.1, R132.2, U31.1 (+)
unnamed: R133.1, R134.2, U32.1 (+)
unnamed: R135.1, TP17.1, U29.3 (-), U29.4
unnamed: R136.1, TP18.1, U30.3 (-), U30.4
unnamed: R137.1, TP19.1, U31.3 (-), U31.4
unnamed: R138.1, TP20.1, U32.3 (-), U32.4
REF1-4: R87.1, R89.1, R91.1, R93.1, TP11.1; also elsewhere on the board
REF5-8: R107.1, R109.1, R111.1, R113.1, TP12.1; also elsewhere on the board

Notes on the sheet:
fg = 1kHz
Vout = Vin * 0.25 Vout @0V: 0V Vout @12V: 3V
